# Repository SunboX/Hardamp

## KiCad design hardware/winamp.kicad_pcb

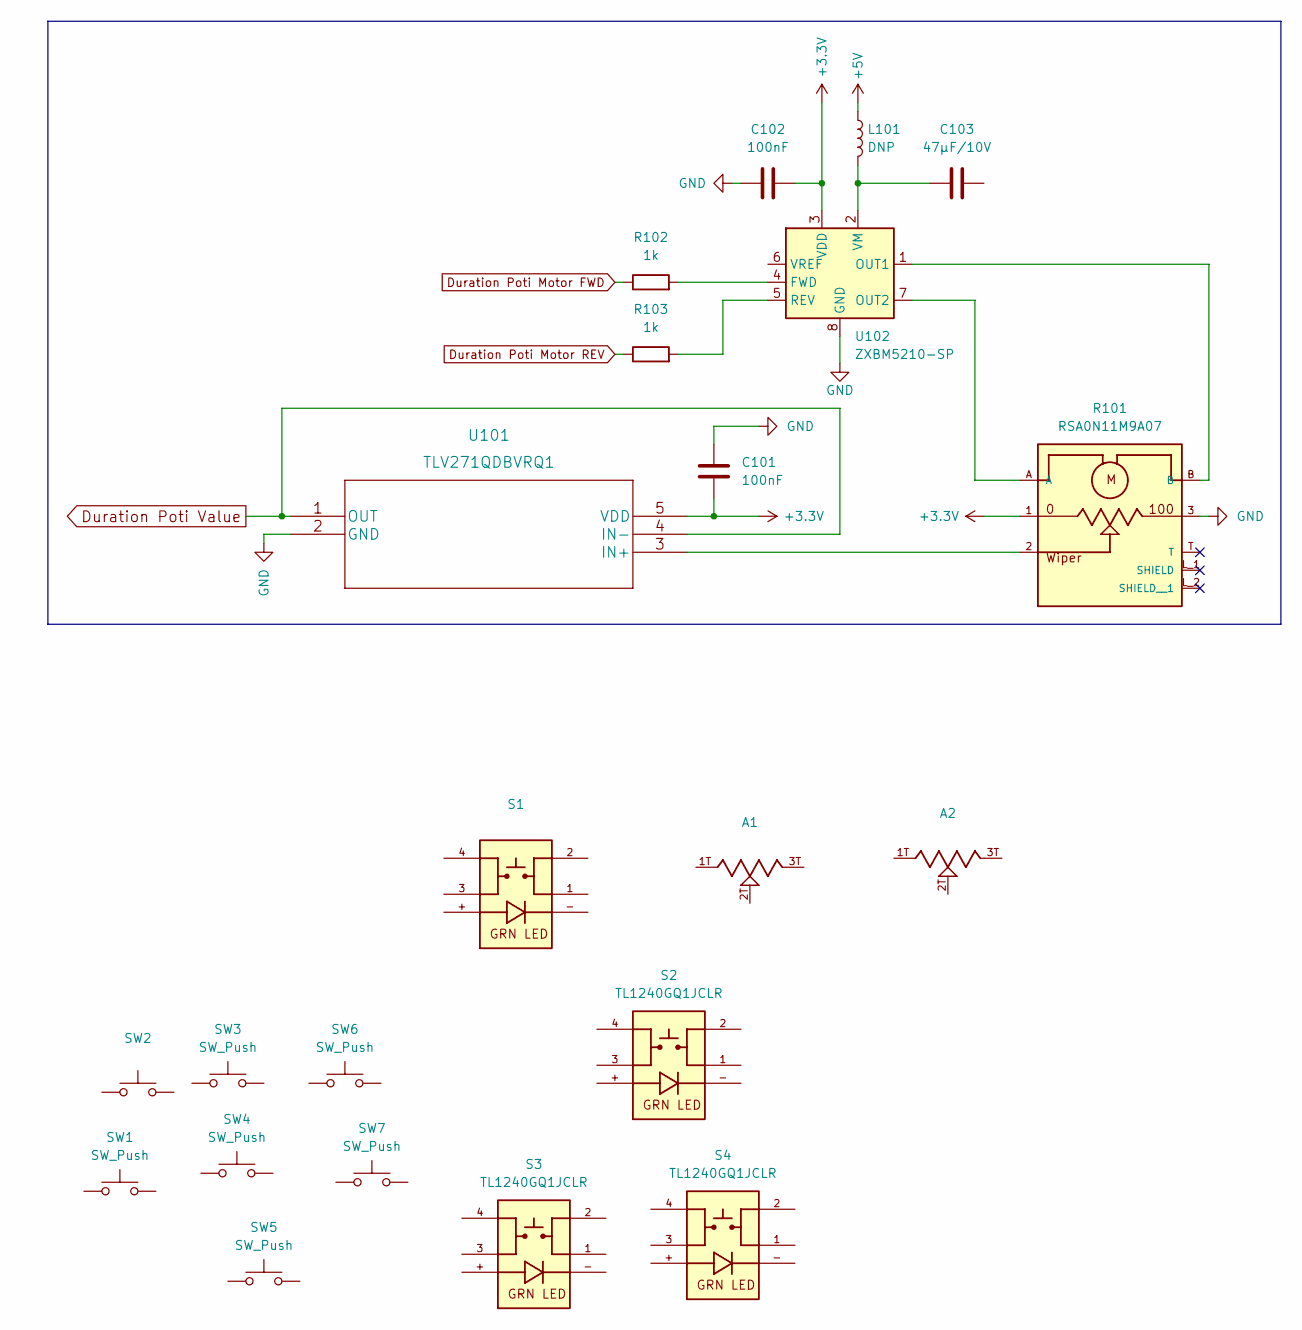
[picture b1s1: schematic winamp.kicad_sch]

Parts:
A1, A2: PARTREV 28/06/21
C101, C102: 100nF; C_0603_1608Metric_Pad1.08x0.95mm_HandSolder
C103: 47µF/10V; C_0603_1608Metric_Pad1.08x0.95mm_HandSolder
L101: DNP
R101: RSA0N11M9A07; TRIM_RSA0N11M9A07; PARTREV N/A
R102, R103: 1k; R_0603_1608Metric_Pad0.98x0.95mm_HandSolder
S1: PARTREV B
S2: TL1240GQ1JCLR; PARTREV B
S3, S4: TL1240GQ1JCLR; SW_TL1240GQ1JCLR; PARTREV B
SW1, SW3, SW4, SW5, SW6, SW7: SW_Push
SW2: (no value)
U101: TLV271QDBVRQ1
U102: ZXBM5210-SP; Diodes_SO-8EP

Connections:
+3V3: C101.2, C102.2, R101.1, U101.5 (VDD), U102.3 (VDD)
Duration Poti Motor FWD: R102.1
Duration Poti Motor REV: R103.1
Duration Poti Value: U101.1 (OUT), U101.4 (IN-)
GND: C101.1, C102.1, R101.3, U101.2 (GND), U102.8 (GND), U102.9 (GND)
unnamed: C103.1, L101.2, U102.2 (VM)
unnamed: R101.2, U101.3 (IN+)
unnamed: R101.A, U102.7 (OUT2)
unnamed: R101.B, U102.1 (OUT1)
unnamed: R102.2, U102.4 (FWD)
unnamed: R103.2, U102.5 (REV)

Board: 2 copper layers, 21 parts (0 on the bottom side), 9 nets, no tracks yet.

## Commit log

2023-04-09 alternative display test

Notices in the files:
hardware/winamp.kicad_pcb:
Copyright (©) 2023 André Fiedler
